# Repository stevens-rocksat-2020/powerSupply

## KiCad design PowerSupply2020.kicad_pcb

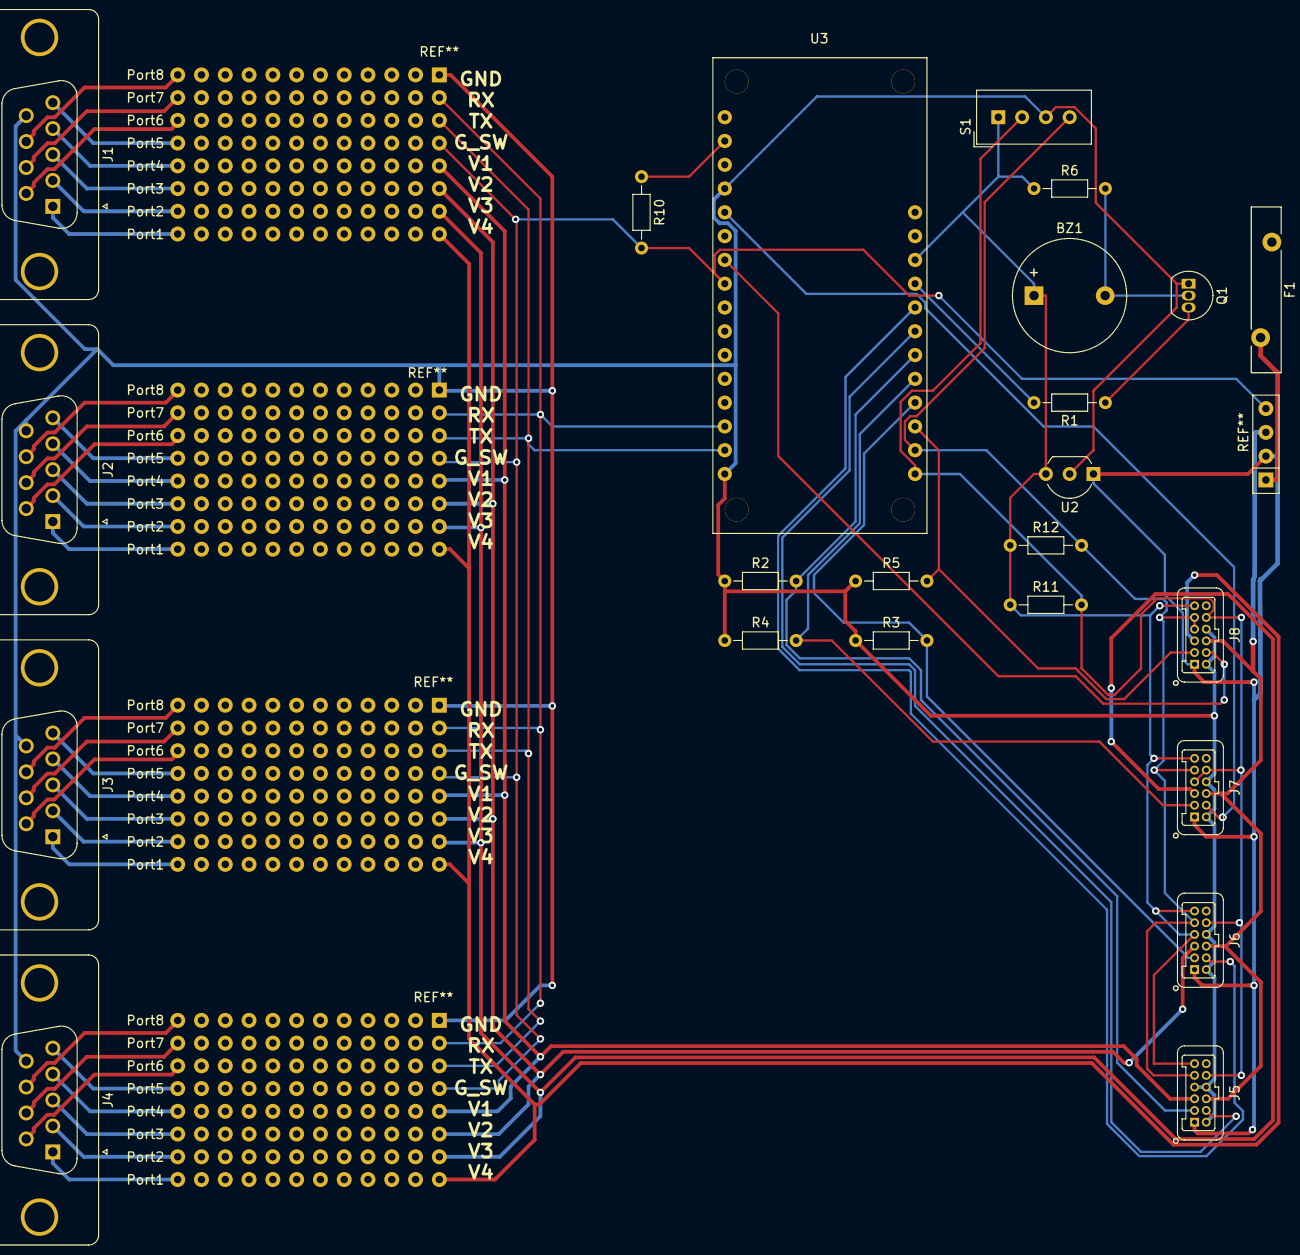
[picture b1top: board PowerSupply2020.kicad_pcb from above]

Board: 2 copper layers, 23 parts (0 on the bottom side), 19 nets.

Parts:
BZ1: Buzzer; Buzzer_12x9.5RM7.6
F1: 3544-2; Fuse_Bourns_MF-RHT1000
J1, J2, J3, J4: DB9_Female; DSUB-9_Female_Vertical_P2.77x2.84mm_MountingHoles
J5: Slave Address 1000000; Harwin_Gecko-G125-FVX1205L0X_2x06_P1.25mm_Vertical
J6: Slave Address 1000001; Harwin_Gecko-G125-FVX1205L0X_2x06_P1.25mm_Vertical
J7: Slave Address 1000010; Harwin_Gecko-G125-FVX1205L0X_2x06_P1.25mm_Vertical
J8: Slave Address 1000011; Harwin_Gecko-G125-FVX1205L0X_2x06_P1.25mm_Vertical
Q1: 2SC1815; TO-92_Inline
R1, R6: 1 kΩ; R_Axial_DIN0204_L3.6mm_D1.6mm_P7.62mm_Horizontal
R2, R3, R4, R5, R10, R11, R12: 10 kΩ; R_Axial_DIN0204_L3.6mm_D1.6mm_P7.62mm_Horizontal
S1: TH_Sensor; Aosong_DHT11_5.5x12.0_P2.54mm
U2: L7805; TO-92_Inline_Wide
U3: Adafruit_Feather_M0_DOA; Adafruit_M0_DOA

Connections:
+3V3: R10.1, U3.15
+5V: BZ1.1, J5.11, J6.7, J6.11, J7.11, J8.11, R6.1, R11.1, R12.1, S1.1, U2.3, U3.26
+12C: J5.1, J6.1, J7.1, J8.1, U2.1
+12V: J5.6, J6.6, J7.6, J8.6
/BUZZ: R1.2, U3.25
/G_SW: R10.2, U3.9
/PG_1: J5.4, U3.23
/PG_2: J6.4, U3.24
/PG_3: J7.4, U3.12
/PG_4: J8.4, U3.10
/SCL: J5.9, J6.9, J7.9, J8.7, J8.9, R12.2, S1.4, U3.18
/SDA: J5.10, J6.10, J7.7, J7.10, J8.10, R11.2, S1.2, U3.17
EN_1: J5.3, R2.2, U3.22
EN_2: J6.3, R3.2, U3.20
EN_3: J7.3, R4.2, U3.21
EN_4: J8.3, R5.2, U3.19
Earth: J1.9, J2.9, J3.9, J4.9, J5.2, J5.7, J5.8, J6.2, J6.8, J7.2, J7.8, J8.2, J8.8, Q1.1, R2.1, R3.1, R4.1, R5.1, S1.3, U2.2, U3.1, U3.13
unnamed: BZ1.2, Q1.2, R6.2
unnamed: Q1.3, R1.1

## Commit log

2020-04-02 Added Alex's changes
